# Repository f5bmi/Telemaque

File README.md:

# Telemaque
 Current, voltage, temperature, forward and reverse signals conditioning.
 
 THIS PROJECT IS STILL UNDER DEVELOPMENT AND NOT VALID FOR PRODUCTION

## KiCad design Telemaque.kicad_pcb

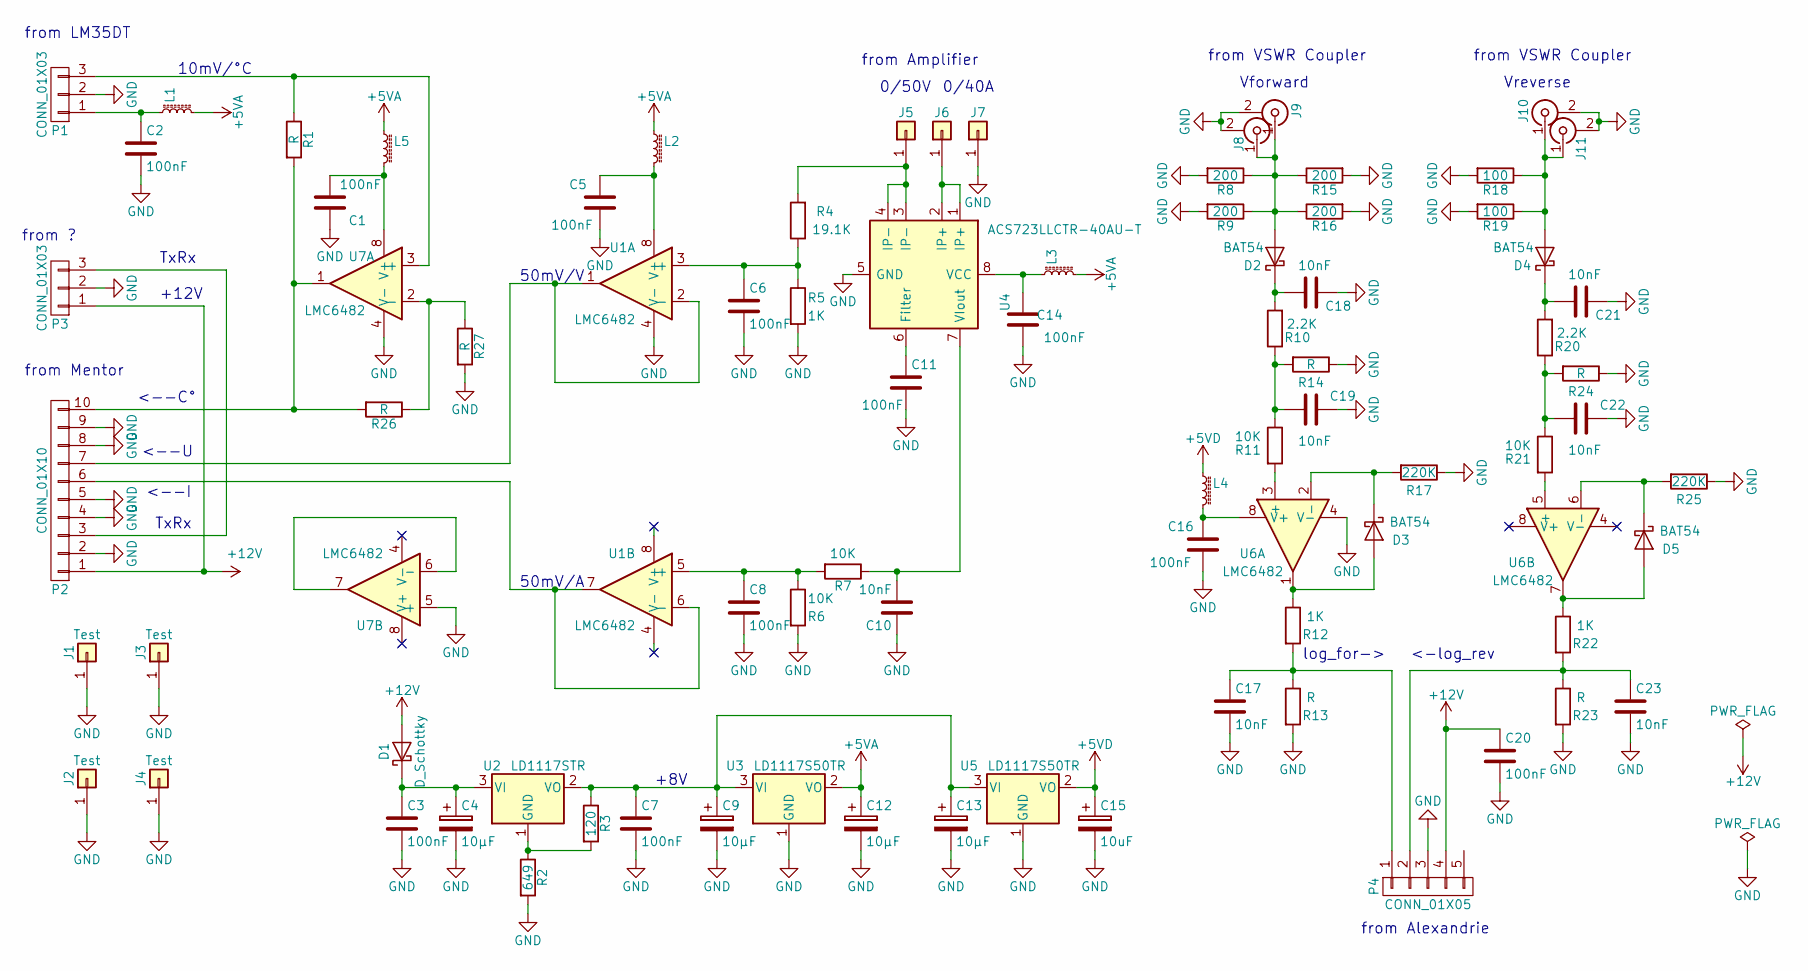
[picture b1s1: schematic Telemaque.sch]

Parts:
C1, C2, C3, C5, C6, C7, C8, C11, C14, C16, C20: 100nF; C_0805_HandSoldering
C4, C9, C12, C13: 10µF; CP_Tantalum_Case-C_EIA-6032-28_Hand
C10, C17, C18, C19, C21, C22, C23: 10nF; R_0805_HandSoldering
C15: 10uF; CP_Tantalum_Case-C_EIA-6032-28_Hand
D1: D_Schottky; D_SMB_Handsoldering
D2, D3, D4, D5: BAT54; D_SOT-23_ANK
J1, J2, J3, J4: Test; MountingHole_3.5mm
J5, J6, J7: Conn_01x01; Wurth
J8, J10: Conn_Coaxial; SMA_PINS
J9, J11: Conn_Coaxial; SMA_EDGE_NRW
L1, L2, L3, L4, L5: L_Core_Ferrite_Small; L_0805_HandSoldering
P1: CONN_01X03; Molex_KK-6410-03_03x2.54mm_Straight
P2: CONN_01X10; Molex_KK-6410-10_10x2.54mm_Straight
P3: CONN_01X03
P4: CONN_01X05; Molex_KK-6410-05_05x2.54mm_Straight
R1, R13, R14, R23, R24, R26, R27: R; R_0805_HandSoldering
R2: 649; R_0805_HandSoldering
R3: 120; R_0805_HandSoldering
R4: 19.1K; R_0805_HandSoldering
R5, R12, R22: 1K; R_0805_HandSoldering
R6, R7, R11, R21: 10K; R_0805_HandSoldering
R8, R9, R15, R16: 200; R_1206_HandSoldering
R10, R20: 2.2K; R_0805_HandSoldering
R17, R25: 220K; R_0805_HandSoldering
R18, R19: 100; R_1206_HandSoldering
U1, U6, U7: LMC6482; SO-8_5.3x6.2mm_Pitch1.27mm
U2: LD1117STR; SOT-223-3Lead_TabPin2
U3, U5: LD1117S50TR; SOT-223-3Lead_TabPin2
U4: ACS723LLCTR-40AU-T; SO-8_5.3x6.2mm_Pitch1.27mm

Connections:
+5VA: C12.1, L1.2, L2.1, L3.2, L5.1, U3.2 (VO)
+5VD: C15.1, L4.1, U5.2 (VO)
+12V: C20.1, D1.2 (A), P2.1, P3.1, P4.4
GND: C1.2, C2.2, C3.2, C4.2, C5.2, C6.2, C7.2, C8.2, C9.2, C10.1, C11.2, C12.2, C13.2, C14.1, C15.2, C16.2, C17.2, C18.1, C19.1, C20.2, C21.1, C22.1, C23.2, J1.1, J2.1, J3.1, J4.1, J7.1, J8.2 (Ext), J9.2 (Ext), J10.2 (Ext), J11.2 (Ext), P1.2, P2.2, P2.4, P2.5, P2.8, P2.9, P3.2, P4.3, R2.2, R5.2, R6.2, R8.2, R9.2, R13.2, R14.1, R15.2, R16.2, R17.1, R18.2, R19.2, R23.2, R24.1, R25.1, R27.2, U1.4 (V-), U3.1 (GND), U4.5 (GND), U5.1 (GND), U6.4 (V-), U7.4 (V-), U7.5 (+)
unnamed: C1.1, L5.2, U7.8 (V+)
unnamed: C2.1, L1.1, P1.1
unnamed: C3.1, C4.1, D1.1 (K), U2.3 (VI)
unnamed: C5.1, L2.2, U1.8 (V+)
unnamed: C6.1, R4.1, R5.1, U1.3 (+)
unnamed: C8.1, R6.1, R7.2, U1.5 (+)
unnamed: C10.2, R7.1, U4.7 (VIout)
unnamed: C11.1, U4.6 (Filter)
unnamed: C7.1, C9.1, C13.1, R3.1, U2.2 (VO), U3.3 (VI), U5.3 (VI)
unnamed: C14.2, L3.1, U4.8 (VCC)
unnamed: C16.1, L4.2, U6.8 (V+)
unnamed: C17.1, P4.1, R12.2, R13.1
unnamed: C18.2, D2.1 (K), R10.2
unnamed: C19.2, R10.1, R11.1, R14.2
unnamed: C21.2, D4.1 (K), R20.2
unnamed: C22.2, R20.1, R21.1, R24.2
unnamed: C23.1, P4.2, R22.2, R23.1
unnamed: D2.2 (A), J8.1 (In), J9.1 (In), R8.1, R9.1, R15.1, R16.1
unnamed: D3.1 (K), R17.2, U6.2 (-)
unnamed: D3.2 (A), R12.1, U6.1
unnamed: D4.2 (A), J10.1 (In), J11.1 (In), R18.1, R19.1
unnamed: D5.1 (K), R25.2, U6.6 (-)
unnamed: D5.2 (A), R22.1, U6.7
unnamed: J5.1, R4.2, U4.3 (IP-), U4.4 (IP-)
unnamed: J6.1, U4.1 (IP+), U4.2 (IP+)
unnamed: P1.3, R1.1, U7.3 (+)
unnamed: P2.3, P3.3
unnamed: P2.6, U1.6 (-), U1.7
unnamed: P2.7, U1.1, U1.2 (-)
unnamed: P2.10, R1.2, R26.2, U7.1
unnamed: R2.1, R3.2, U2.1 (GND)
unnamed: R11.2, U6.3 (+)
unnamed: R21.2, U6.5 (+)
unnamed: R26.1, R27.1, U7.2 (-)
unnamed: U7.6 (-), U7.7

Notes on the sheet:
Vforward
Vreverse
from Mentor
<--U
<--I
<--C°
from LM35DT
from Amplifier
from VSWR Coupler
log_for->
<-log_rev
from Alexandrie
0/50V
0/40A
TxRx
+8V
10mV/°C
50mV/V
50mV/A
from ?
+12V

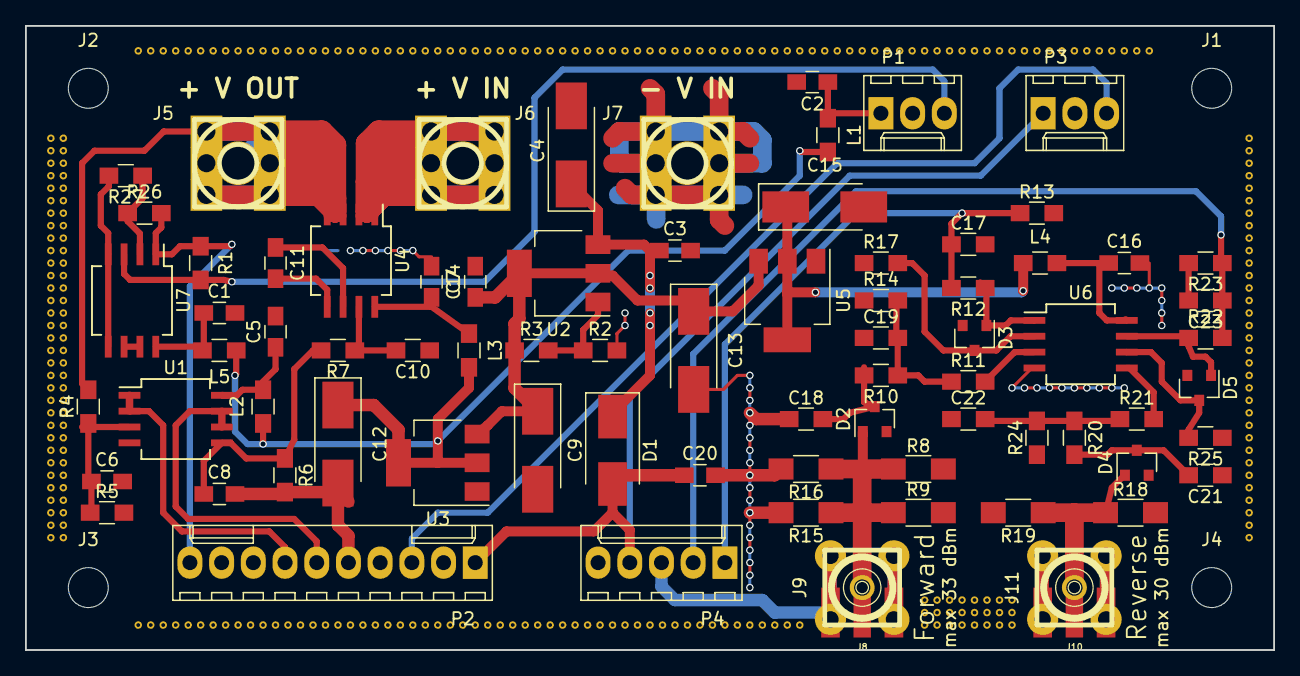
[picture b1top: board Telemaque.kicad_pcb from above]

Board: 2 copper layers, 100.0 x 50.0 mm, 82 parts (0 on the bottom side), 39 nets.
